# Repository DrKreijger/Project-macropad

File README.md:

# Project-macropad
 Macropad project

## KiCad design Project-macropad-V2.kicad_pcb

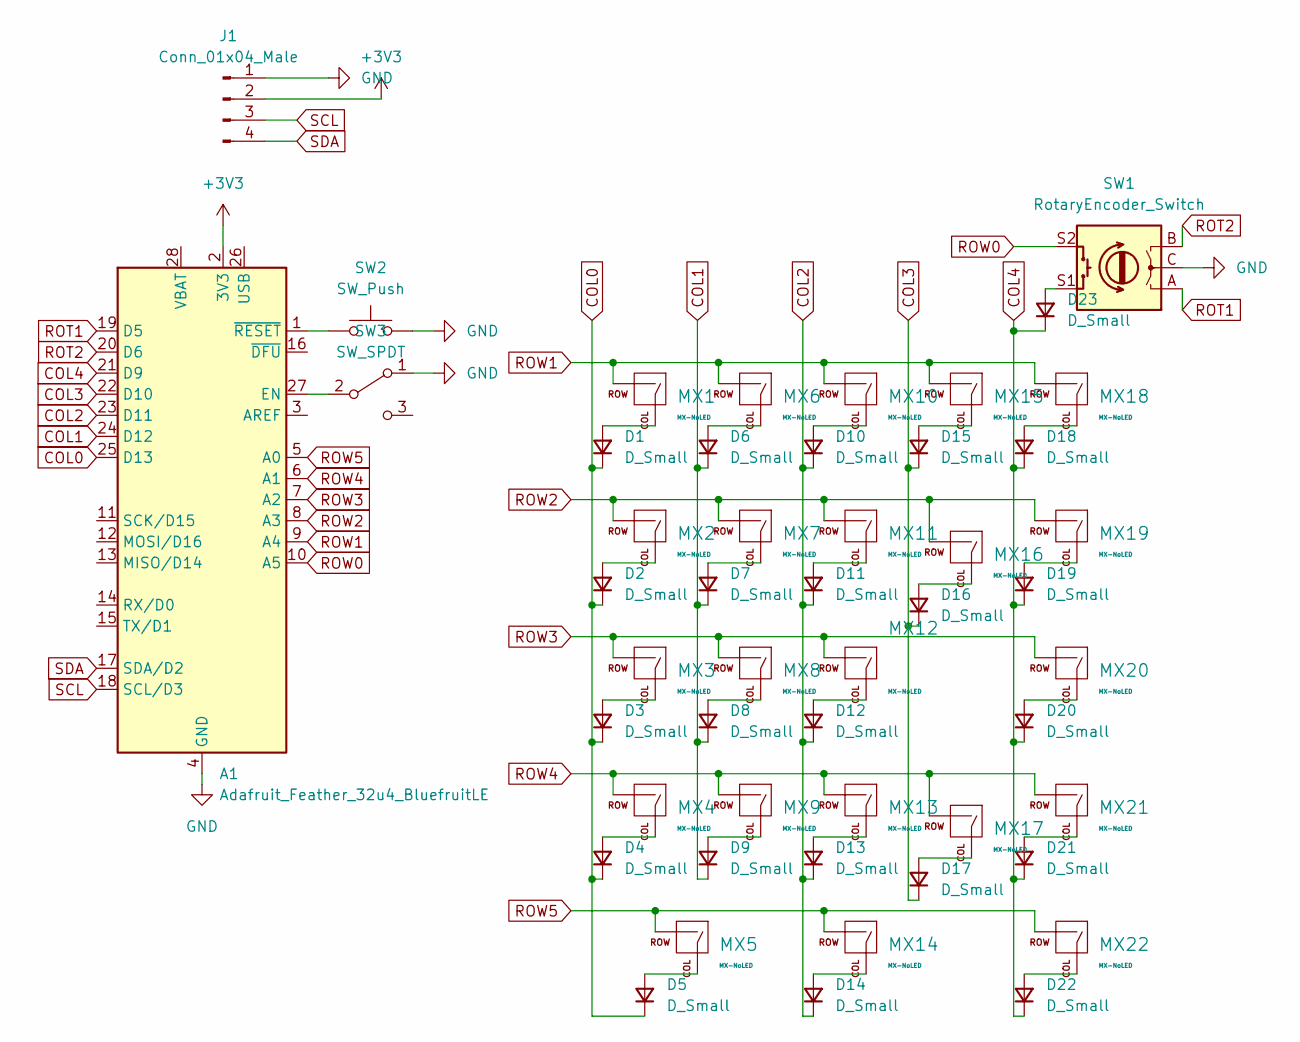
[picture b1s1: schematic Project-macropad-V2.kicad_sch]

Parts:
A1: Adafruit_Feather_32u4_BluefruitLE; Adafruit_Feather
D1, D2, D3, D4, D5, D6, D7, D8, D9, D10, D11, D12, D13, D14, D15, D16, D17, D18, D19, D20, D21, D22, D23: D_Small; D_DO-35_SOD27_P7.62mm_Horizontal
J1: Conn_01x04_Male; SSD1306-0.91-OLED-4pin-128x32
MX1, MX2, MX3, MX4, MX6, MX7, MX8, MX9, MX10, MX11, MX12, MX13, MX14, MX15, MX18, MX19, MX20, MX21, MX22: MX-NoLED; MX-1U-NoLED
MX5, MX16, MX17: MX-NoLED; MX-2U-NoLED
SW1: RotaryEncoder_Switch; RotaryEncoder_Alps_EC11E-Switch_Vertical_H20mm_CircularMoun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
SW2: SW_Push; SKQG-1155865
SW3: SW_SPDT; SW_Slide_1P2T_CK_OS102011MS2Q

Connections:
+3V3: A1.2 (3V3), J1.2
COL0: A1.25 (D13), D1.1 (K), D2.1 (K), D3.1 (K), D4.1 (K), D5.1 (K)
COL1: A1.24 (D12), D6.1 (K), D7.1 (K), D8.1 (K), D9.1 (K)
COL2: A1.23 (D11), D10.1 (K), D11.1 (K), D12.1 (K), D13.1 (K), D14.1 (K)
COL3: A1.22 (D10), D15.1 (K), D16.1 (K), D17.1 (K)
COL4: A1.21 (D9), D18.1 (K), D19.1 (K), D20.1 (K), D21.1 (K), D22.1 (K), D23.1 (K)
GND: A1.4 (GND), J1.1, SW1.C, SW2.2, SW3.1 (A)
unnamed: A1.1 (~RESET), SW2.1
unnamed: A1.27 (EN), SW3.2 (B)
unnamed: D1.2 (A), MX1.1 (COL)
unnamed: D2.2 (A), MX2.1 (COL)
unnamed: D3.2 (A), MX3.1 (COL)
unnamed: D4.2 (A), MX4.1 (COL)
unnamed: D5.2 (A), MX5.1 (COL)
unnamed: D6.2 (A), MX6.1 (COL)
unnamed: D7.2 (A), MX7.1 (COL)
unnamed: D8.2 (A), MX8.1 (COL)
unnamed: D9.2 (A), MX9.1 (COL)
unnamed: D10.2 (A), MX10.1 (COL)
unnamed: D11.2 (A), MX11.1 (COL)
unnamed: D12.2 (A), MX12.1 (COL)
unnamed: D13.2 (A), MX13.1 (COL)
unnamed: D14.2 (A), MX14.1 (COL)
unnamed: D15.2 (A), MX15.1 (COL)
unnamed: D16.2 (A), MX16.1 (COL)
unnamed: D17.2 (A), MX17.1 (COL)
unnamed: D18.2 (A), MX18.1 (COL)
unnamed: D19.2 (A), MX19.1 (COL)
unnamed: D20.2 (A), MX20.1 (COL)
unnamed: D21.2 (A), MX21.1 (COL)
unnamed: D22.2 (A), MX22.1 (COL)
unnamed: D23.2 (A), SW1.S1
ROT1: A1.19 (D5), SW1.A
ROT2: A1.20 (D6), SW1.B
ROW0: A1.10 (A5), SW1.S2
ROW1: A1.9 (A4), MX1.2 (ROW), MX6.2 (ROW), MX10.2 (ROW), MX15.2 (ROW), MX18.2 (ROW)
ROW2: A1.8 (A3), MX2.2 (ROW), MX7.2 (ROW), MX11.2 (ROW), MX16.2 (ROW), MX19.2 (ROW)
ROW3: A1.7 (A2), MX3.2 (ROW), MX8.2 (ROW), MX12.2 (ROW), MX20.2 (ROW)
ROW4: A1.6 (A1), MX4.2 (ROW), MX9.2 (ROW), MX13.2 (ROW), MX17.2 (ROW), MX21.2 (ROW)
ROW5: A1.5 (A0), MX5.2 (ROW), MX14.2 (ROW), MX22.2 (ROW)
SCL: A1.18 (SCL/D3), J1.3
SDA: A1.17 (SDA/D2), J1.4

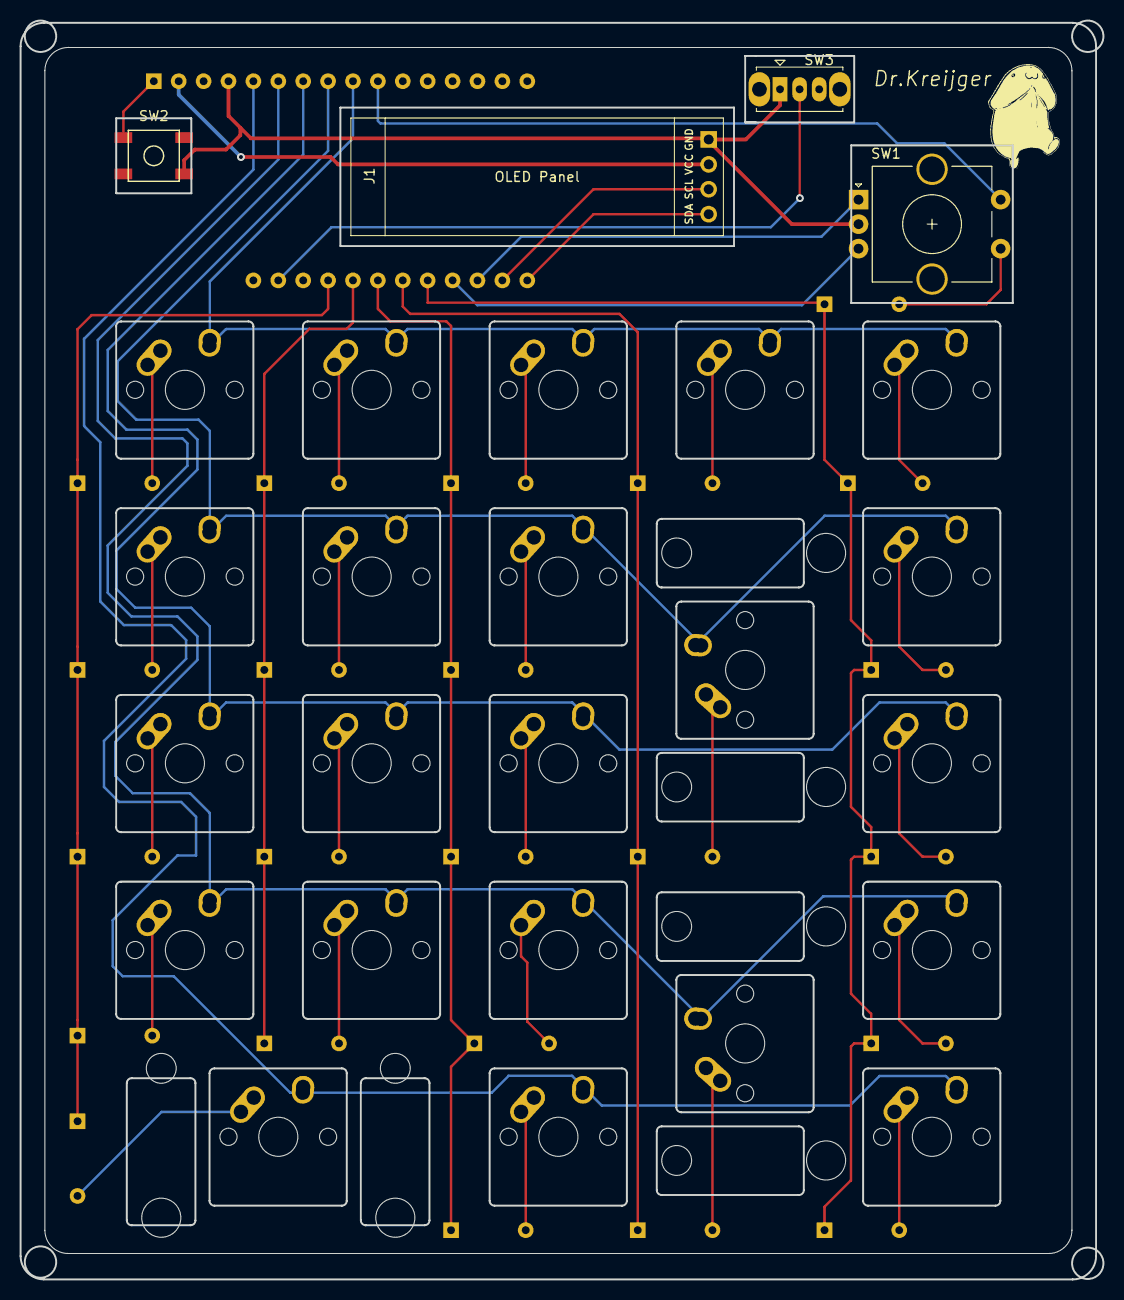
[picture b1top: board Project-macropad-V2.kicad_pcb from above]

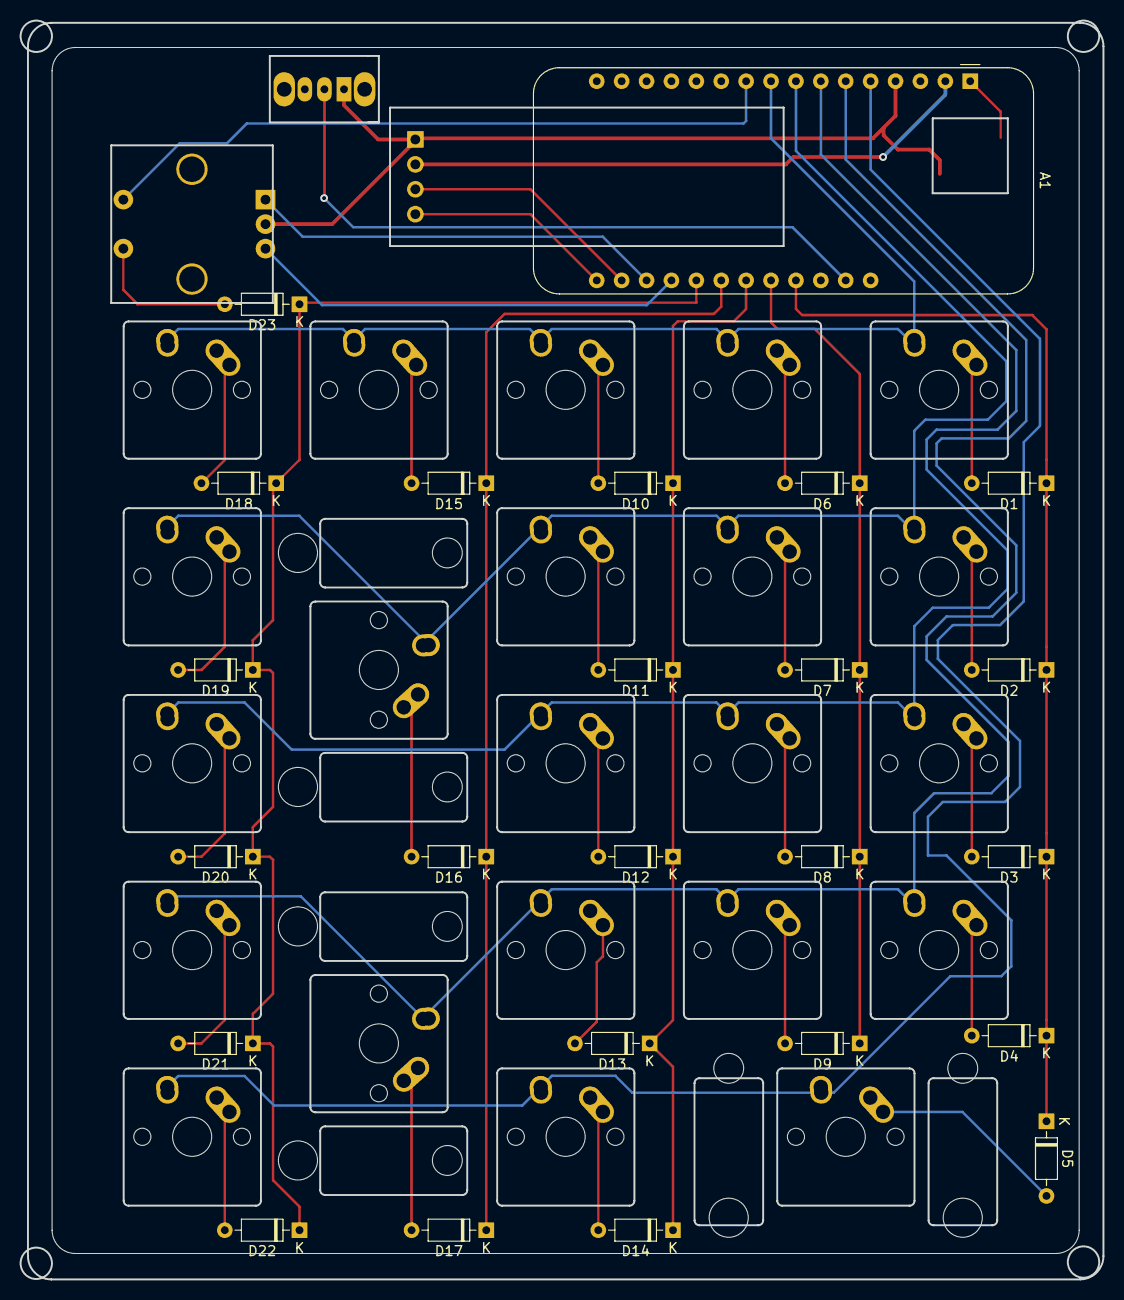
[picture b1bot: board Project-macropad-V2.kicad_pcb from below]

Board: 2 copper layers, 110.5 x 128.4 mm, 50 parts (24 on the bottom side), 42 nets.

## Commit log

2022-10-28 Base
2022-10-28 Library added
2022-10-29 Matrix start
2022-10-29 Schematic done
2022-10-29 PCB Diodes and Switches
2022-10-30 PCB Routing done
2022-10-30 Finished PCB
2022-11-01 Case start
2022-11-01 Plate almost done
2022-11-02 Plate done
2022-11-12 Firmware done
2022-12-11 Case done
    Case done and some garbage removed
2023-08-21 Update transfer new pc
